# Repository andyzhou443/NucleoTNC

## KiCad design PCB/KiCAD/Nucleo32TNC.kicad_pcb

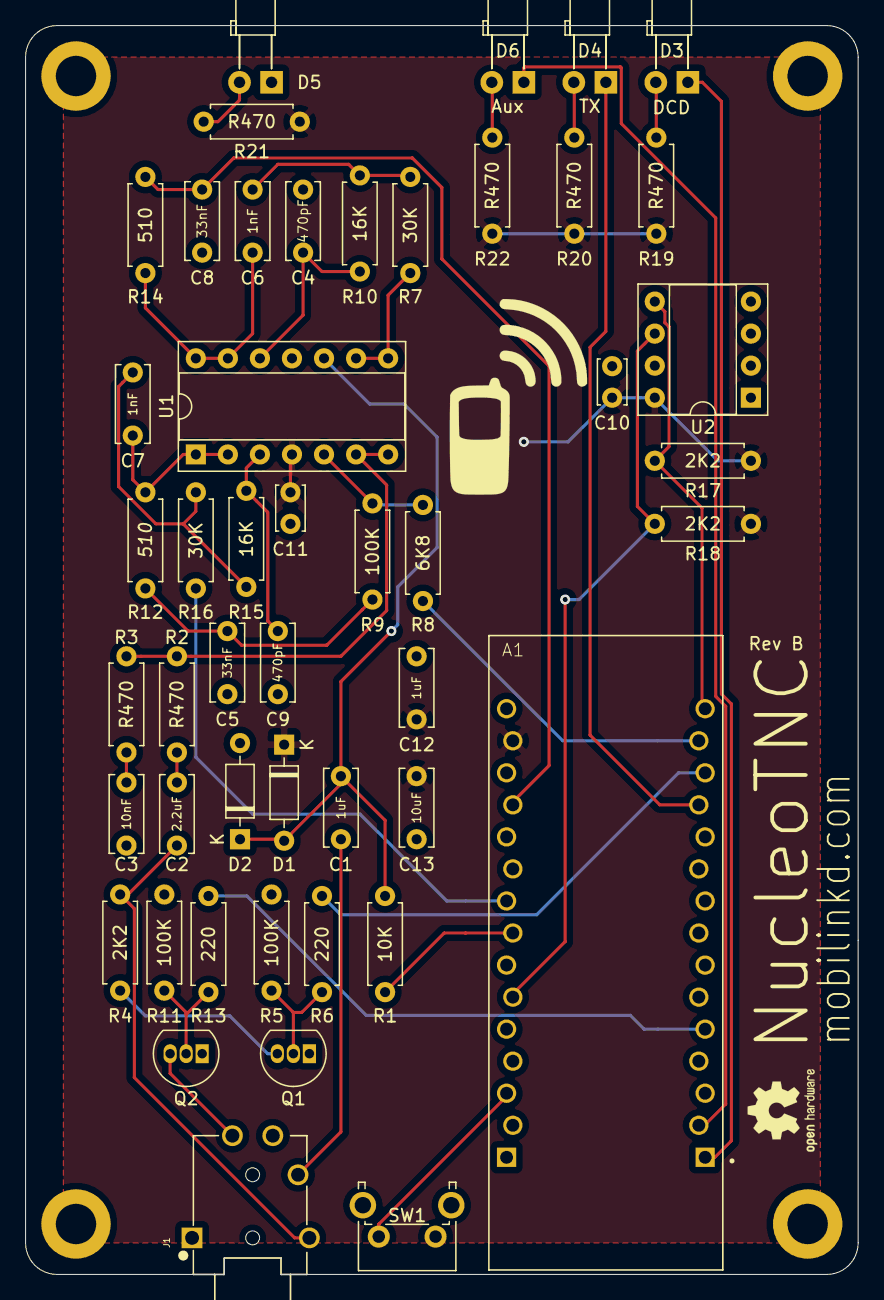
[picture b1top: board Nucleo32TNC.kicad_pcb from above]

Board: 2 copper layers, 66.0 x 99.0 mm, 53 parts (0 on the bottom side), 37 nets.

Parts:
A1: NUCLEO-L432KC; MODULE_NUCLEO-L432KC
C1, C12: 1uF; C_Disc_D6.0mm_W2.5mm_P5.00mm
C2: 2.2uF; C_Disc_D6.0mm_W2.5mm_P5.00mm
C3: 10nF; C_Disc_D6.0mm_W2.5mm_P5.00mm
C4, C9: 470pF; C_Disc_D6.0mm_W2.5mm_P5.00mm
C5, C8: 33nF; C_Disc_D6.0mm_W2.5mm_P5.00mm
C6, C7: 1nF; C_Disc_D6.0mm_W2.5mm_P5.00mm
C10, C11: 0.1uF; C_Disc_D3.4mm_W2.1mm_P2.50mm
C13: 10uF; C_Disc_D6.0mm_W2.5mm_P5.00mm
D1, D2: BAT85; D_DO-35_SOD27_P7.62mm_Horizontal
D3: DCD; LED_D3.0mm_Horizontal_O3.81mm_Z2.0mm
D4: TX; LED_D3.0mm_Horizontal_O3.81mm_Z2.0mm
D5: BLU LED; LED_D3.0mm_Horizontal_O3.81mm_Z2.0mm
D6: Aux; LED_D3.0mm_Horizontal_O3.81mm_Z2.0mm
G1: LOGO
H1, H2, H3, H4: MountingHole; MountingHole_3.2mm_M3_ISO14580_Pad
J1: SJ-43515TS; CUI_SJ-43515TS
Q1, Q2: 2N7000; TO-92_Inline
R1: 10K; R_Axial_DIN0207_L6.3mm_D2.5mm_P7.62mm_Horizontal
R2, R3, R19, R20, R21, R22: R470; R_Axial_DIN0207_L6.3mm_D2.5mm_P7.62mm_Horizontal
R4, R17, R18: 2K2; R_Axial_DIN0207_L6.3mm_D2.5mm_P7.62mm_Horizontal
R5, R9, R11: 100K; R_Axial_DIN0207_L6.3mm_D2.5mm_P7.62mm_Horizontal
R6, R13: 220; R_Axial_DIN0207_L6.3mm_D2.5mm_P7.62mm_Horizontal
R7, R16: 30K; R_Axial_DIN0207_L6.3mm_D2.5mm_P7.62mm_Horizontal
R8: 6K8; R_Axial_DIN0207_L6.3mm_D2.5mm_P7.62mm_Horizontal
R10, R15: 16K; R_Axial_DIN0207_L6.3mm_D2.5mm_P7.62mm_Horizontal
R12, R14: 510; R_Axial_DIN0207_L6.3mm_D2.5mm_P7.62mm_Horizontal
SW1: PTS645VL58-2 LFS; SW_Tactile_SPST_Angled_PTS645Vx58-2LFS
U1: MCP6004; DIP-14_W7.62mm_Socket
U2: 24LC32; DIP-8_W7.62mm_Socket

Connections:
+3V3: A1.4.14, C10.1, C11.1, C12.1, C13.1, D1.1, R17.1, R18.1, R19.1, R20.1, R21.1, R22.1, U1.4, U2.8
/ADC_AUDIO: A1.4.12, C8.2, R14.1
/AUDIO_ATTEN: A1.3.14, R8.2
/AUDIO_IN: C1.2, J1.T
/AUDIO_OUT: C2.1, J1.R2, R4.2
/DAC_AUDIO: A1.4.9, R16.2
/DC_OFFSET: A1.4.8, R1.2
/I2C_SCL: A1.4.6, R18.2, U2.6
/I2C_SDA: A1.3.15, R17.2, U2.5
/LED_DCD: A1.3.1, D3.1
/LED_MISC: A1.3.2, D6.1
/LED_TX: A1.3.12, D4.1
/PTT: J1.R1, Q2.3
/PTT_MULTIPLEX: A1.3.13, R6.1
/PTT_SIMPLEX: A1.3.5, R13.1
GND: A1.3.4, A1.4.2, C3.1, C4.1, C5.1, C8.1, C9.1, C10.2, C11.2, C12.2, C13.2, D2.2, D5.1, H1.1, H2.1, H3.1, H4.1, J1.S, Q1.1, Q2.1, R5.2, R11.2, SW1.1, U1.11, U2.1, U2.2, U2.3, U2.4, U2.7
unnamed: A1.4.3, SW1.2
unnamed: C1.1, D1.2, D2.1, R1.1, U1.10
unnamed: C2.2, R2.2
unnamed: C3.2, R3.2
unnamed: C4.2, R10.1, U1.12
unnamed: C5.2, R9.1, R12.2
unnamed: C6.1, R14.2, U1.13, U1.14
unnamed: C6.2, R7.1, R10.2
unnamed: C7.1, R15.1, R16.1
unnamed: C7.2, R12.1, U1.1, U1.2
unnamed: C9.2, R15.2, U1.3
unnamed: D3.2, R19.2
unnamed: D4.2, R20.2
unnamed: D5.2, R21.2
unnamed: D6.2, R22.2
unnamed: Q1.2, R5.1, R6.2
unnamed: Q1.3, R4.1
unnamed: Q2.2, R11.1, R13.2
unnamed: R2.1, R3.1, U1.6, U1.7
unnamed: R7.2, U1.8, U1.9
unnamed: R8.1, R9.2, U1.5

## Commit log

2021-03-26 Added FrontPanel.step file
